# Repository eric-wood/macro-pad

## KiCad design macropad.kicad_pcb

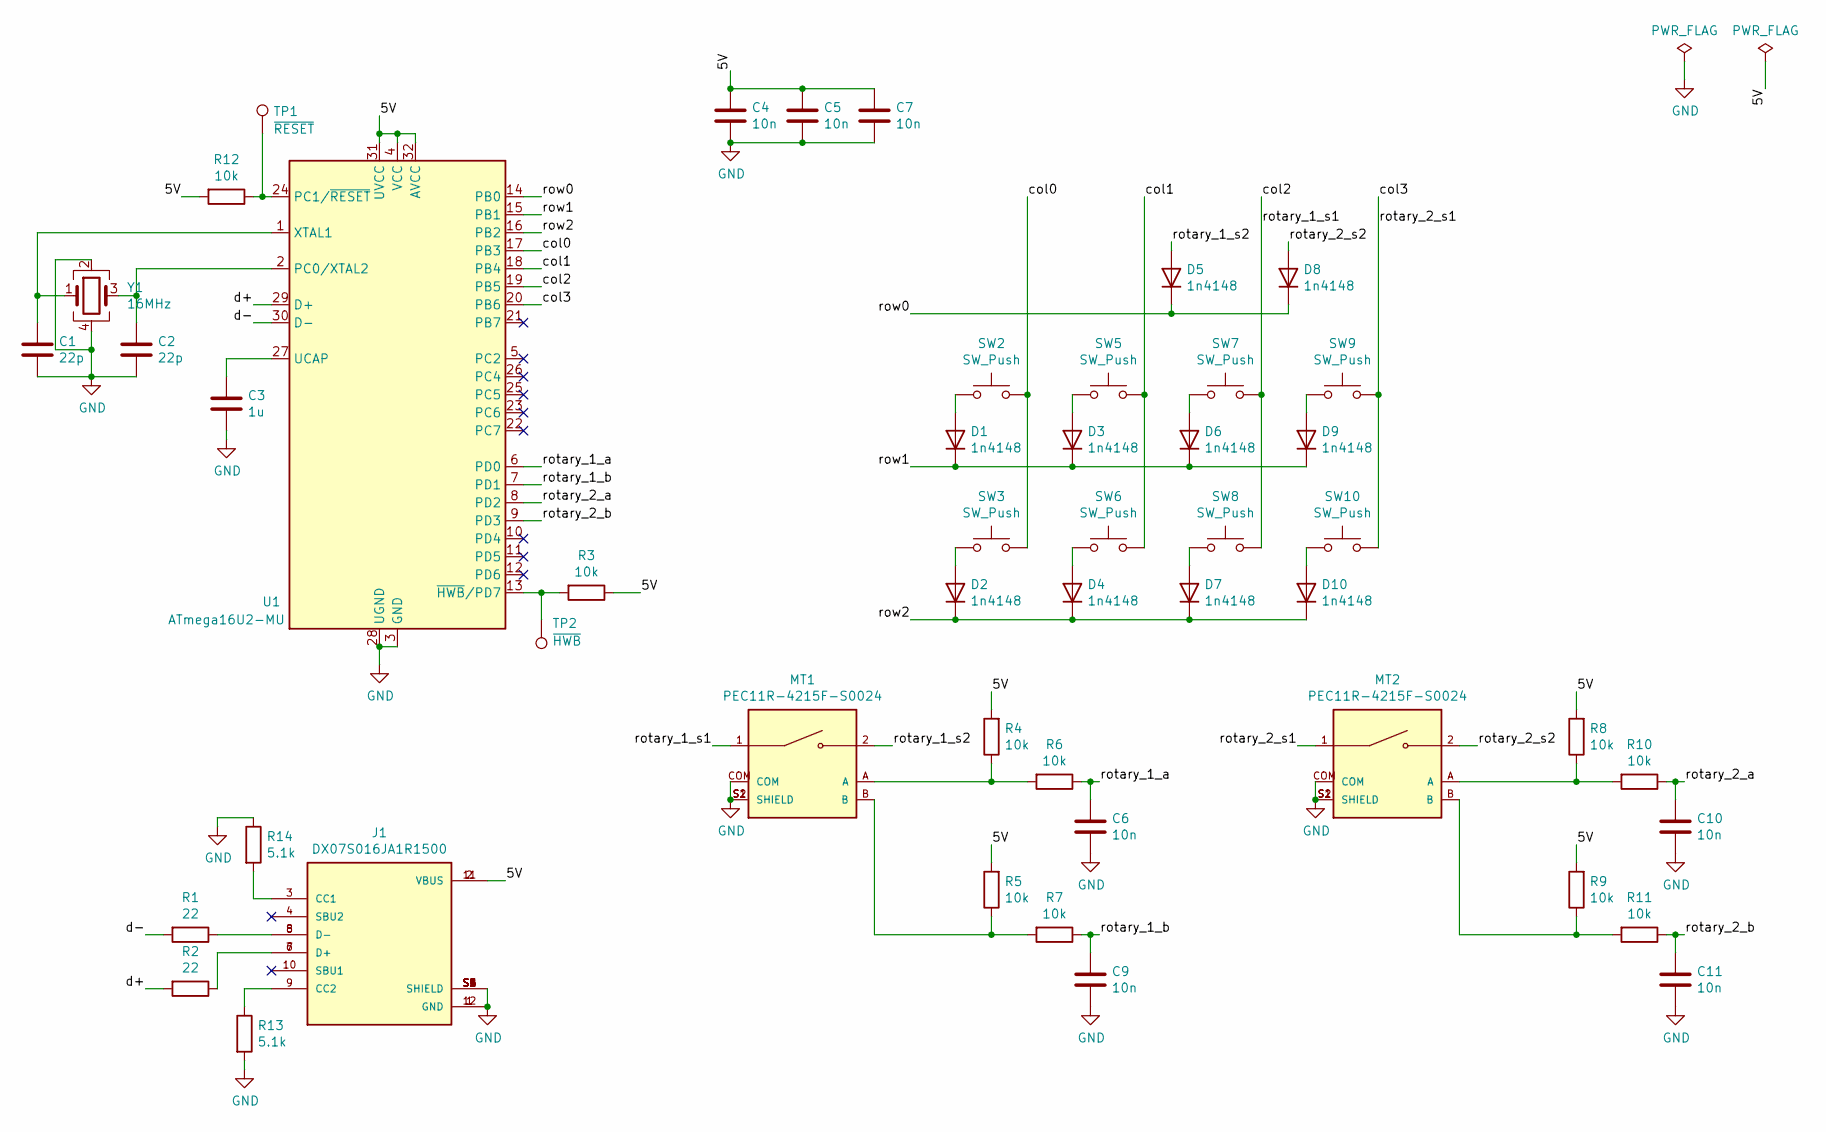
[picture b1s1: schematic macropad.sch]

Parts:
C1, C2: 22p; C_0603_1608Metric; LCSC C1653
C3: 1u; C_0603_1608Metric; LCSC C15849
C4, C5, C6, C7, C9, C10, C11: 10n; C_0603_1608Metric; LCSC C57112
D1, D2, D3, D4, D5, D6, D7, D8, D9, D10: 1n4148; D_SOD-323F; LCSC C2128
J1: DX07S016JA1R1500; JAE_DX07S016JA1R1500; PARTREV 1
MT1, MT2: PEC11R-4215F-S0024; XDCR_PEC11R-4215F-S0024; PARTREV Rev. 09/19
R1, R2: 22; R_0603_1608Metric; LCSC C23345
R3, R4, R5, R6, R7, R8, R9, R10, R11, R12: 10k; R_0603_1608Metric; LCSC C25804
R13, R14: 5.1k; R_0603_1608Metric; LCSC C23186
SW2, SW3, SW5, SW6, SW7, SW8, SW9, SW10: SW_Push; SW_Cherry_MX_1.00u_PCB
TP1: ~RESET; TestPoint_Pad_D1.0mm
TP2: ~HWB; TestPoint_Pad_D1.0mm
U1: ATmega16U2-MU; QFN-32-1EP_5x5mm_P0.5mm_EP3.1x3.1mm; LCSC C17317
Y1: 16MHz; Crystal_SMD_3225-4Pin_3.2x2.5mm; LCSC C13738

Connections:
/5V: C4.1, C5.1, C7.1, J1.2 (VBUS), J1.11 (VBUS), R3.1, R4.2, R5.2, R8.2, R9.2, R12.2, U1.4 (VCC), U1.31 (UVCC), U1.32 (AVCC)
/col0: SW2.2, SW3.2, U1.17 (PB3)
/col1: SW5.2, SW6.2, U1.18 (PB4)
/col2: MT1.1, SW7.2, SW8.2, U1.19 (PB5)
/col3: MT2.1, SW9.2, SW10.2, U1.20 (PB6)
/d+: R2.2, U1.29 (D+)
/d-: R1.2, U1.30 (D-)
/rotary_1_a: C6.1, R6.1, U1.6 (PD0)
/rotary_1_b: C9.1, R7.1, U1.7 (PD1)
/rotary_1_s2: D5.2 (A), MT1.2
/rotary_2_a: C10.1, R10.1, U1.8 (PD2)
/rotary_2_b: C11.1, R11.1, U1.9 (PD3)
/rotary_2_s2: D8.2 (A), MT2.2
/row0: D5.1 (K), D8.1 (K), U1.14 (PB0)
/row1: D1.1 (K), D3.1 (K), D6.1 (K), D9.1 (K), U1.15 (PB1)
/row2: D2.1 (K), D4.1 (K), D7.1 (K), D10.1 (K), U1.16 (PB2)
GND: C1.2, C2.2, C3.2, C4.2, C5.2, C6.2, C7.2, C9.2, C10.2, C11.2, J1.1 (GND), J1.12 (GND), J1.S1 (SHIELD), J1.S2 (SHIELD), J1.S3 (SHIELD), J1.S4 (SHIELD), J1.S5 (SHIELD), J1.S6 (SHIELD), MT1.COM, MT1.S1 (SHIELD), MT1.S2 (SHIELD), MT2.COM, MT2.S1 (SHIELD), MT2.S2 (SHIELD), R13.2, R14.1, U1.3 (GND), U1.28 (UGND), U1.33 (GND), Y1.2, Y1.4
unnamed: C1.1, U1.1 (XTAL1), Y1.1
unnamed: C2.1, U1.2 (PC0/XTAL2), Y1.3
unnamed: C3.1, U1.27 (UCAP)
unnamed: D1.2 (A), SW2.1
unnamed: D2.2 (A), SW3.1
unnamed: D3.2 (A), SW5.1
unnamed: D4.2 (A), SW6.1
unnamed: D6.2 (A), SW7.1
unnamed: D7.2 (A), SW8.1
unnamed: D9.2 (A), SW9.1
unnamed: D10.2 (A), SW10.1
unnamed: J1.3 (CC1), R14.2
unnamed: J1.5 (D-), J1.8 (D-), R1.1
unnamed: J1.6 (D+), J1.7 (D+), R2.1
unnamed: J1.9 (CC2), R13.1
unnamed: MT1.A, R4.1, R6.2
unnamed: MT1.B, R5.1, R7.2
unnamed: MT2.A, R8.1, R10.2
unnamed: MT2.B, R9.1, R11.2
unnamed 38: R3.2, TP2.1, U1.13 (~HWB~/PD7); also elsewhere on the board
unnamed 39: R12.1, TP1.1, U1.24 (PC1/~RESET); also elsewhere on the board

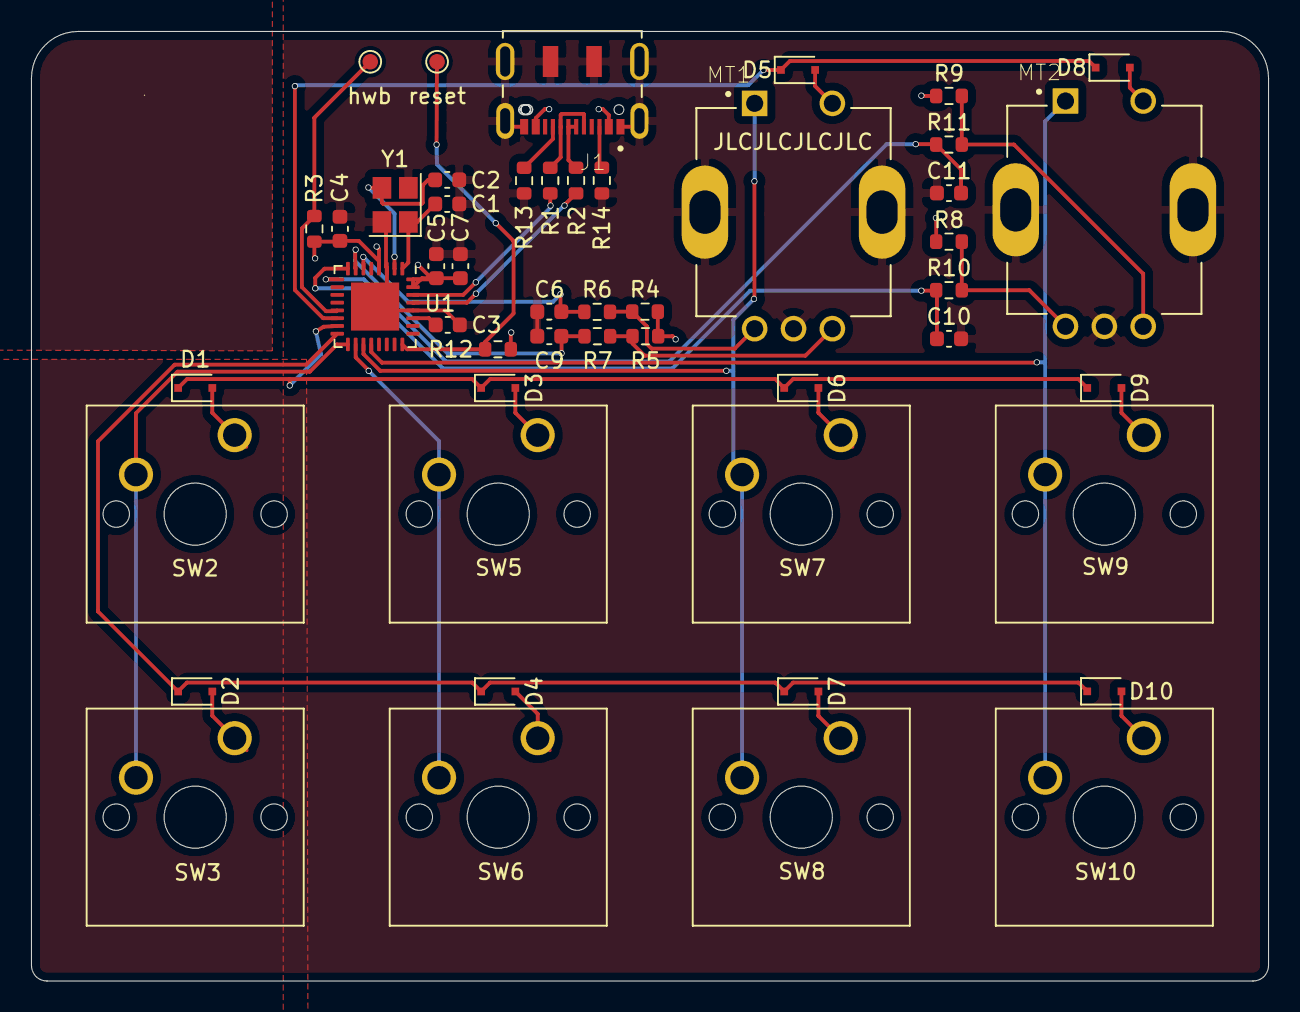
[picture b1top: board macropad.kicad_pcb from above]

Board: 2 copper layers, 79.6 x 61.1 mm, 49 parts (0 on the bottom side), 38 nets.

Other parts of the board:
hwb: ~HWB; TestPoint_Pad_D1.0mm
reset: ~RESET; TestPoint_Pad_D1.0mm

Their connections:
unnamed 38: hwb.1; also elsewhere on the board
unnamed 39: reset.1; also elsewhere on the board

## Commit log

2021-03-09 Schematic done
2021-03-09 use actual models
2021-03-09 seems like a good place to leave it for today
2021-03-10 Improvements
2021-03-10 Fix everything forever
2021-03-10 Some aesthetic cleanup
2021-03-10 Finalized layout
2021-03-11 copper frankie
2021-03-11 Generate fab files
2021-03-11 missed a spot
2021-03-11 Add JLC to silkscreen
2021-03-11 Cleanup
2021-03-24 Fix bugs discovered in first board
2021-03-24 Add v2 and plot gerbers
